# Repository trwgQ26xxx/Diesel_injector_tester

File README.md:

# Diesel Injector Tester

**A small tester generating short 200 µs pulses needed for testing the opening of electromagnetic diesel injectors with a selectable repetition period.**

Generates high-current, short pulses (200us) with a selectable repetition rate: 0.2Hz, 0.5Hz, 1Hz, 2Hz, 5Hz, or 10Hz.

The tester is operated using two buttons:

* *ENABLE* - Toggles the high-current output on or off.
* *PERIOD* - Cycles through available repetition rates.

Status is indicated by two LEDs:

* *PERIOD* LED blinks at the selected repetition rate.
* *ENABLE* LED is lit when the high-current output is active.

# Disclaimer

I do not consent to the use of all or part of the project for commercial purposes!

Nie wyrażam zgody na wykorzystanie całości bądź części projektu w celach zarobkowych!

# License

Shield: [![CC BY-NC-SA 4.0][cc-by-nc-sa-shield]][cc-by-nc-sa]

This work is licensed under a
[Creative Commons Attribution-NonCommercial-ShareAlike 4.0 International License][cc-by-nc-sa].

[![CC BY-NC-SA 4.0][cc-by-nc-sa-image]][cc-by-nc-sa]

[cc-by-nc-sa]: http://creativecommons.org/licenses/by-nc-sa/4.0/
[cc-by-nc-sa-image]: https://licensebuttons.net/l/by-nc-sa/4.0/88x31.png
[cc-by-nc-sa-shield]: https://img.shields.io/badge/License-CC%20BY--NC--SA%204.0-lightgrey.svg

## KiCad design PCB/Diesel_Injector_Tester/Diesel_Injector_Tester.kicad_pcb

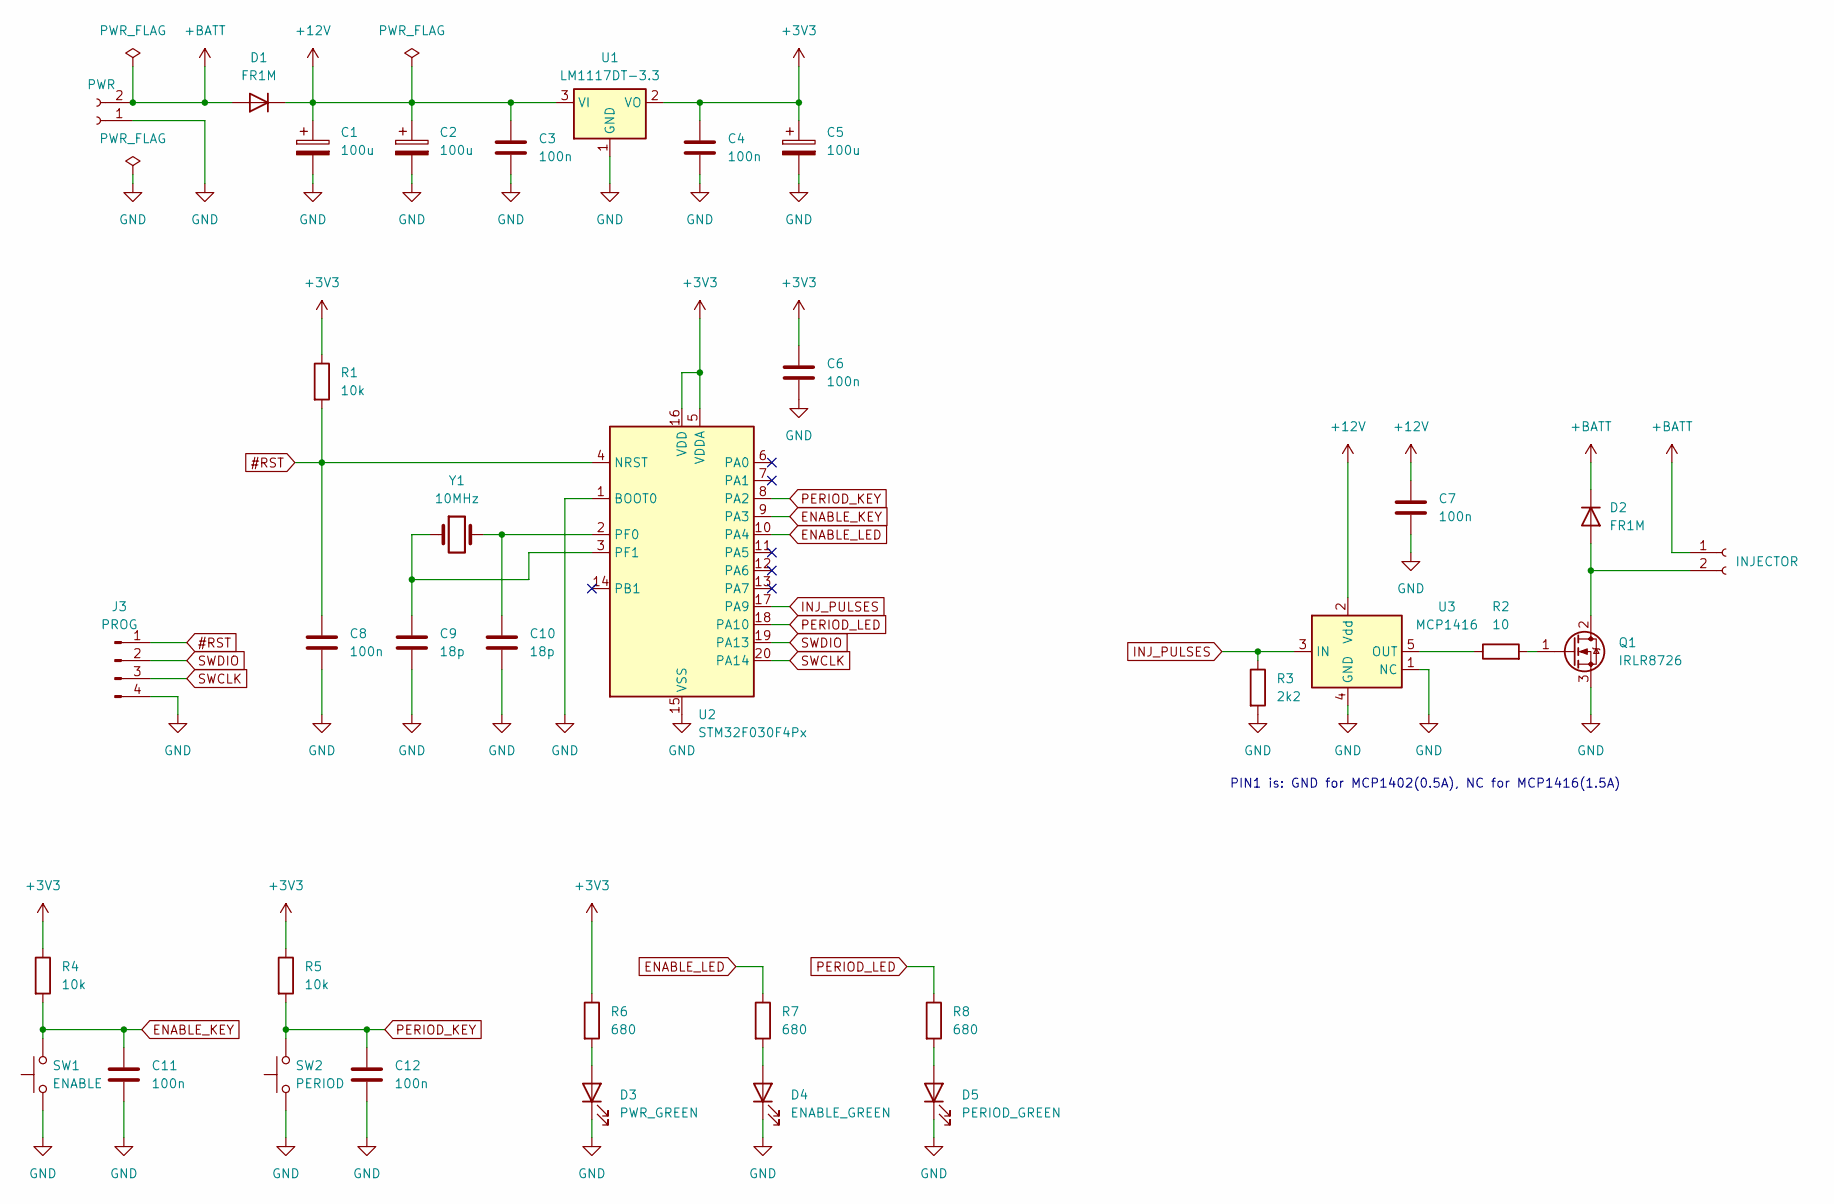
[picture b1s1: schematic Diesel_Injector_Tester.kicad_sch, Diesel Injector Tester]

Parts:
C1, C2: 100u; CP_Elec_8x6.5
C3, C4, C6, C7, C8, C11, C12: 100n; C_0805_2012Metric_Pad1.18x1.45mm_HandSolder
C5: 100u; CP_Elec_6.3x5.8
C9, C10: 18p; C_0805_2012Metric_Pad1.18x1.45mm_HandSolder
D1, D2: FR1M; D_SMA
D3: PWR_GREEN; LED_1206_3216Metric_Pad1.42x1.75mm_HandSolder
D4: ENABLE_GREEN; LED_1206_3216Metric_Pad1.42x1.75mm_HandSolder
D5: PERIOD_GREEN; LED_1206_3216Metric_Pad1.42x1.75mm_HandSolder
J1: PWR; TerminalBlock_bornier-2_P5.08mm
J2: INJECTOR; TerminalBlock_bornier-2_P5.08mm
J3: PROG; PinSocket_1x04_P2.54mm_Vertical
Q1: IRLR8726; TO-252-3_TabPin2
R1, R4, R5: 10k; R_0805_2012Metric_Pad1.20x1.40mm_HandSolder
R2: 10; R_0805_2012Metric_Pad1.20x1.40mm_HandSolder
R3: 2k2; R_0805_2012Metric_Pad1.20x1.40mm_HandSolder
R6, R7, R8: 680; R_0805_2012Metric_Pad1.20x1.40mm_HandSolder
SW1: ENABLE; SW_SPST_PTS645
SW2: PERIOD; SW_SPST_PTS645
U1: LM1117DT-3.3; TO-252-3_TabPin2
U2: STM32F030F4Px; TSSOP-20_4.4x6.5mm_P0.65mm
U3: MCP1416; SOT-23-5
Y1: 10MHz; Crystal_SMD_HC49-SD_HandSoldering

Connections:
#RST: C8.1, J3.1, R1.2, U2.4 (NRST)
+3V3: C4.1, C5.1, C6.1, R1.1, R4.1, R5.1, R6.1, U1.2 (VO), U2.5 (VDDA), U2.16 (VDD)
+12V: C1.1, C2.1, C3.1, C7.1, D1.1 (K), U1.3 (VI), U3.2 (Vdd)
+BATT: D1.2 (A), D2.1 (K), J1.2, J2.1
ENABLE_KEY: C11.1, R4.2, SW1.2, U2.9 (PA3)
ENABLE_LED: R7.1, U2.10 (PA4)
GND: C1.2, C2.2, C3.2, C4.2, C5.2, C6.2, C7.2, C8.2, C9.2, C10.2, C11.2, C12.2, D3.1 (K), D4.1 (K), D5.1 (K), J1.1, J3.4, Q1.3 (S), R3.2, SW1.1, SW2.1, U1.1 (GND), U2.1 (BOOT0), U2.15 (VSS), U3.1 (NC), U3.4 (GND)
INJ_PULSES: R3.1, U2.17 (PA9), U3.3 (IN)
unnamed: D2.2 (A), J2.2, Q1.2 (D)
unnamed: D3.2 (A), R6.2
unnamed: D4.2 (A), R7.2
unnamed: D5.2 (A), R8.2
unnamed: Q1.1 (G), R2.2
unnamed: C10.1, U2.2 (PF0), Y1.2
unnamed: C9.1, U2.3 (PF1), Y1.1
unnamed: R2.1, U3.5 (OUT)
PERIOD_KEY: C12.1, R5.2, SW2.2, U2.8 (PA2)
PERIOD_LED: R8.1, U2.18 (PA10)
SWCLK: J3.3, U2.20 (PA14)
SWDIO: J3.2, U2.19 (PA13)

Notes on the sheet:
PIN1 is: GND for MCP1402(0.5A), NC for MCP1416(1.5A)

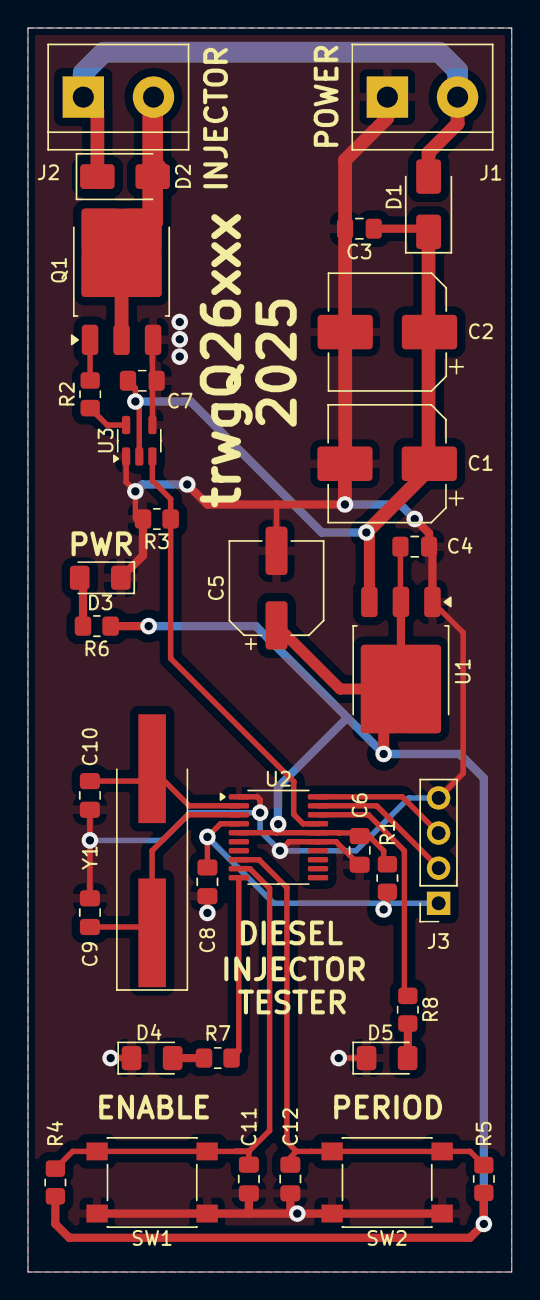
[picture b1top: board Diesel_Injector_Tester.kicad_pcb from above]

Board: 2 copper layers, 35.0 x 90.0 mm, 35 parts (0 on the bottom side), 20 nets.

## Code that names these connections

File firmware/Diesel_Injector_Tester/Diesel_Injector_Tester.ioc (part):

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Mcu.Name=STM32F030F4Px
Mcu.Package=TSSOP20
Mcu.UserName=STM32F030F4Px
PA0.GPIOParameters=GPIO_PuPd
PA0.GPIO_PuPd=GPIO_PULLUP
PA0.Signal=GPIO_Input
PA1.GPIOParameters=GPIO_PuPd
PA1.GPIO_PuPd=GPIO_PULLUP
PA1.Signal=GPIO_Input
PA10.GPIOParameters=GPIO_Speed,GPIO_Label
PA10.GPIO_Label=PERIOD_LED
PA10.GPIO_Speed=GPIO_SPEED_FREQ_HIGH
PA10.Signal=S_TIM1_CH3
PA13.GPIOParameters=GPIO_PuPd
PA13.GPIO_PuPd=GPIO_PULLUP
PA13.Signal=GPIO_Input
PA14.GPIOParameters=GPIO_PuPd
PA14.GPIO_PuPd=GPIO_PULLUP
PA14.Signal=GPIO_Input
PA2.GPIOParameters=GPIO_PuPd,GPIO_Label
PA2.GPIO_Label=PERIOD_KEY
PA2.GPIO_PuPd=GPIO_PULLUP
PA2.Signal=GPIO_Input
PA3.GPIOParameters=GPIO_PuPd,GPIO_Label
PA3.GPIO_Label=ENABLE_KEY
PA3.GPIO_PuPd=GPIO_PULLUP
PA3.Signal=GPIO_Input
PA4.GPIOParameters=GPIO_Speed,GPIO_Label
PA4.GPIO_Label=ENABLE_LED
PA4.GPIO_Speed=GPIO_SPEED_FREQ_HIGH
PA4.Signal=GPIO_Output
PA5.GPIOParameters=GPIO_PuPd
PA5.GPIO_PuPd=GPIO_PULLUP
PA5.Signal=GPIO_Input
PA6.GPIOParameters=GPIO_PuPd
PA6.GPIO_PuPd=GPIO_PULLUP
PA6.Signal=GPIO_Input
PA7.GPIOParameters=GPIO_PuPd
PA7.GPIO_PuPd=GPIO_PULLUP
PA7.Signal=GPIO_Input
PA9.GPIOParameters=GPIO_Speed,GPIO_Label
PA9.GPIO_Label=INJ_PULSES
PA9.GPIO_Speed=GPIO_SPEED_FREQ_HIGH
PA9.Signal=S_TIM1_CH2
PB1.GPIOParameters=GPIO_PuPd
PB1.GPIO_PuPd=GPIO_PULLUP
PB1.Signal=GPIO_Input
PF0-OSC_IN.Mode=HSE-External-Oscillator
PF0-OSC_IN.Signal=RCC_OSC_IN
PF1-OSC_OUT.Mode=HSE-External-Oscillator
PF1-OSC_OUT.Signal=RCC_OSC_OUT
RCC.HSE_VALUE=10000000
RCC.SYSCLKFreq_VALUE=40000000
RCC.SYSCLKSource=RCC_SYSCLKSOURCE_PLLCLK
board=custom

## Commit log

2025-08-05 Gitignore added
2025-08-05 README.md updated
2025-08-05 Project updated to STM32CubeIDE 1.19.0 and added to repository
2025-08-05 Refactor, code cleanup
2025-08-05 Schematic added, footprints assigned
2025-08-05 Schematic in PDF added
2025-08-23 PCB prepared, schematic updated
2025-09-24 Changed signal names to reflect ones from schematic, changed crystal from 8MHz to 10MHz
2025-09-24 Changed ENABLE_LED logic to reflect schematic
2025-09-25 Schematic updated for final component values
2025-09-25 Photos updated
2025-09-25 Photos fixed
2025-09-25 README.md typo fixed
2025-09-25 Update related to GERBER files generation
